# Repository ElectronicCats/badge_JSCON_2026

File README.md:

# Badge JSCONF 2026

Hardware abierto del **badge de JSCONF México 2026** (Guadalajara, 29 y 30 de octubre), diseñado por [Electronic Cats](https://electroniccats.com).

Es un nodo de radio **LoRa** con pantalla a color y cuatro botones que funciona como un nodo más de una red [Meshtastic](https://meshtastic.org): sirve de gafete con tu nombre, manda mensajes de texto a otros badges sin red celular ni Wi-Fi, y trae un juego de ajolotes que se desbloquean al encontrarte con otras personas.

Este repositorio contiene el **diseño de hardware** (esquemático, PCB y huellas). El firmware, las herramientas y la presentación del taller viven en otros repositorios (ver [Proyectos relacionados](#proyectos-relacionados)).

## Características

| Elemento | Detalle |
|-|-|
| Microcontrolador | ESP32-S3-WROOM-1-N8 (8 MB de flash, sin PSRAM), USB nativo |
| Radio | Módulo LoRa de 915 MHz (LLCC68), antena por conector SMA de borde |
| Pantalla | 428 × 142 px a color, conector FFC de 10 pines |
| Botones | 4 de usuario (arriba, abajo, select, back) y un interruptor de encendido |
| Alimentación | USB-C, con fusible de 0.75 A y regulador de 3.3 V. Sin batería ni GPS |
| Conectividad | LoRa (malla), Bluetooth LE (app de Meshtastic) y USB CDC (control desde el navegador) |
| PCB | 2 capas, 1.6 mm, diseñada en KiCad 10 |

## Estructura del repositorio

```text
.
├── hardware/                        # Proyecto de KiCad
│   ├── Badge_JSCON_2026.kicad_pro
│   ├── Badge_JSCON_2026.kicad_sch   # Esquemático
│   ├── Badge_JSCON_2026.kicad_pcb   # PCB
│   ├── Footprints/                  # Huellas, símbolos y modelos 3D propios
│   ├── fp-lib-table
│   ├── electroniccats_sch.kibot.yaml
│   └── electroniccats_pcb.kibot.yaml
├── docs/images/                     # Fotos del badge para este README
└── .github/workflows/               # Generación automática de archivos de fabricación
```

## Hardware

### KiCad

El hardware se diseña en **KiCad 10** (el proyecto fue guardado con la versión 10.0). Los archivos que genera el diseño son:

- `Badge_JSCON_2026.kicad_pro`
- `Badge_JSCON_2026.kicad_pcb`
- `Badge_JSCON_2026.kicad_sch`

Los archivos temporales de KiCad los ignora Git ([archivos ignorados](.gitignore)). Todo lo del diseño va dentro de la carpeta [hardware](hardware/).

Las huellas y símbolos que no vienen en las bibliotecas estándar (módulo LoRa, pantalla, conector USB-C, antena SMA, interruptor, ESP32-S3) están en [hardware/Footprints](hardware/Footprints/) y se cargan con `fp-lib-table`.

### Componentes principales

| Ref. | Valor | Función |
|-|-|-|
| U1 | ESP32-S3-WROOM-1-N8 | Microcontrolador, Bluetooth LE y USB |
| U5 | VGdd79S915N0S1 | Módulo LoRa 915 MHz |
| U2 | BL8072CLTR33 (SOT-223) | Regulador de 3.3 V |
| P1 | USB-C (C393939) | Alimentación y datos |
| F1 | Fusible 0.75 A | Protección de entrada |
| J2 | FFC 10 pines (Hirose FH12) | Pantalla |
| Q2 | BC846 | Control de brillo de la pantalla (`LCD_BRIGHT`) |
| SW1, SW2, SW4–SW7 | Pulsadores SMD TL3342 | Cuatro botones de usuario, BOOT y EN (reset) |
| SW3 | MSK12C02 | Interruptor de encendido |
| AE1 | Conector SMA de borde | Antena LoRa |
| R1, R2 | 5.1 kΩ | Configuración del USB-C |

La lista completa de materiales (BOM) se genera automáticamente en cada release.

### Configuración de automatización

Los workflows de GitHub Actions detectan automáticamente los archivos de KiCad en `hardware/`; no hace falta modificar ningún archivo de configuración.

Buscan:
- El primer archivo `.kicad_pcb` encontrado en `hardware/`.
- El archivo `.kicad_sch` que coincida con el nombre del PCB.
- Si no hay coincidencia exacta, el primer `.kicad_sch` disponible.

**Nota**: los archivos de KiCad deben estar en la carpeta `hardware/` con sus extensiones correctas (`.kicad_pro`, `.kicad_pcb`, `.kicad_sch`).

**Workflows disponibles:**
- **DRC y ERC**: se ejecutan en cada `push` y `pull_request` para validar el diseño.
- **Archivos de fabricación**: se generan cuando se publica un `release`.

#### Activar o desactivar DRC y ERC

Están activos por defecto. Para desactivarlos, cambia estas líneas en [electroniccats_sch.kibot.yaml](hardware/electroniccats_sch.kibot.yaml):

```yaml
run_erc: false  # Cambiar a false para desactivar ERC
run_drc: false  # Cambiar a false para desactivar DRC
```

### Creación de un release

Al terminar el proyecto y su revisión se publica el release:

1. Presiona **Create a new release**.
2. Revisa la sección de **Actions**: ahí se generan los archivos.
3. Al terminar, los archivos de fabricación (Gerbers, taladros, BOM y BOM interactivo, posición de componentes, modelo STEP y PDF del esquemático y del PCB) quedan adjuntos al mismo release.

## Cómo funciona el badge

Con el firmware del taller, el badge:

- Se anuncia en las apps de Meshtastic como un nodo normal (por Bluetooth LE, con PIN de 6 dígitos que muestra la pantalla).
- Usa el preset `SHORT_FAST` en la región US, fijos. Por eso **no interopera con la malla pública** de Meshtastic, solo con otros badges del evento.
- Se puede controlar desde el navegador por USB con Web Serial (mostrar textos, pulsar botones, cambiar el nombre, subir una imagen de 428 × 142).

Los detalles del firmware, el juego de ajolotes, las páginas de la pantalla y cómo flashear un badge están en el repositorio del firmware.

## Proyectos relacionados

| Proyecto | Qué contiene |
|-|-|
| [jscon-2026-firmware](https://github.com/ElectronicCats/jscon-2026-firmware) | Firmware (fork de Meshtastic con el target `badge_jscon2026`) |
| [presentacion-jscon-2026](https://github.com/ElectronicCats/presentacion-jscon-2026) | Presentación del taller |
| [Tienda de Electronic Cats](https://electroniccats.com/store/badgejsconf-taller/) | Badge y taller de JSCONF |
| [JSCONF México](https://www.jsconf.mx/) | Evento |

## Licencia y créditos

- **Diseño de hardware:** Lizeth Gallegos Martínez, Electronic Cats (rev. v1.0).
- **Presentadores del taller:** Andrés Sabas y Heikki Isa Perea Esparza.
- **Evento:** JSCONF México 2026.

## Maintainer

Electronic Cats invests time and resources providing this open source design, please support Electronic Cats and open-source hardware by purchasing products from Electronic Cats!

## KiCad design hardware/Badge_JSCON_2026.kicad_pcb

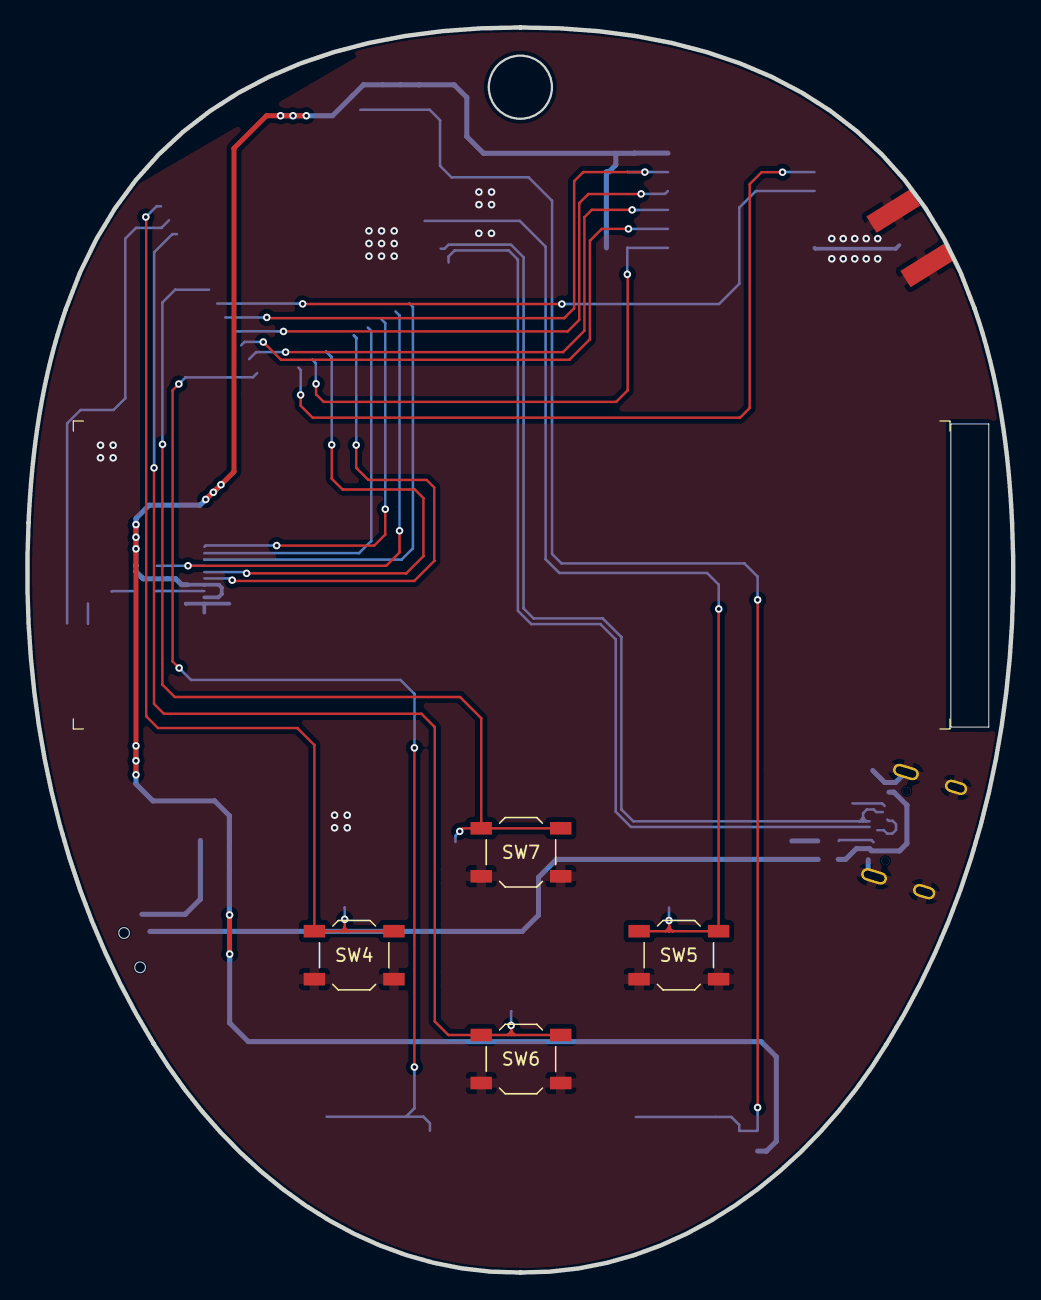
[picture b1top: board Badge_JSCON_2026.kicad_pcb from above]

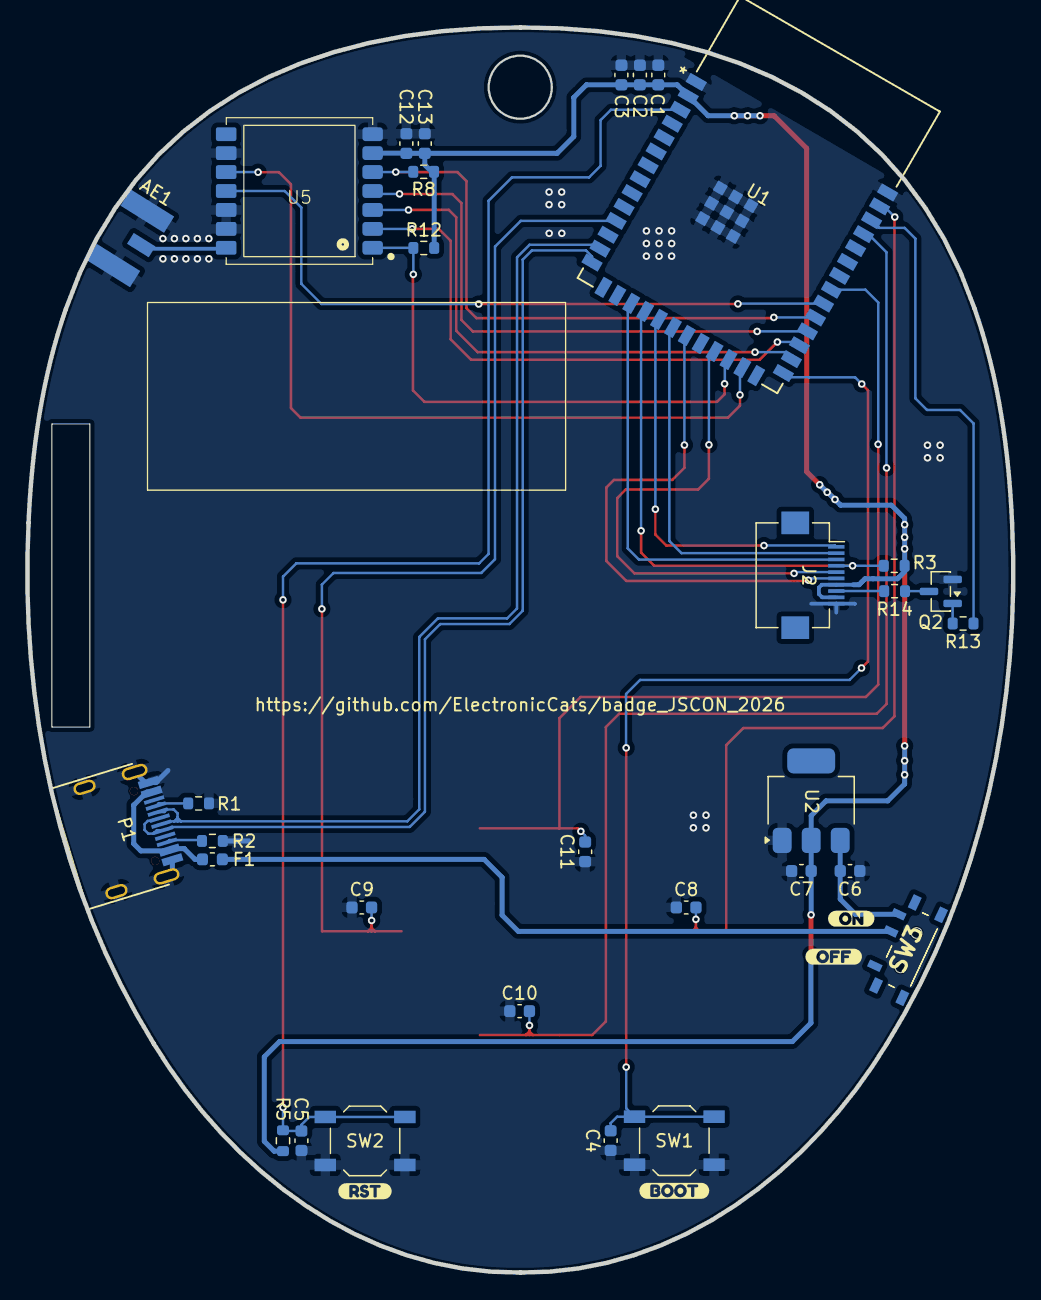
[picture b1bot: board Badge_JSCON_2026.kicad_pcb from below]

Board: 2 copper layers, 78.1 x 98.6 mm, 40 parts (36 on the bottom side), 33 nets.

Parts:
AE1: Antenna_Shield; SMA_EDGE
C1: 1uF; C_0603_1608Metric
C2, C3, C6, C7, C13: 10uF; C_0603_1608Metric
C4, C5, C8, C9, C10, C11: 0.1uF; C_0603_1608Metric
C12: 100nF; C_0603_1608Metric
F1: 0.75A; Fuse_0603_1608Metric
J2: LCD; Hirose_FH12-10S-0.5SH_1x10-1MP_P0.50mm_Horizontal
P1: USB_C_Plug_USB2.0; C393939
Q2: BC846; SOT-23
R1, R2: 5k1; R_0603_1608Metric
R3, R5, R8, R12: 10K; R_0603_1608Metric
R13: 1K; R_0603_1608Metric
R14: 3.9r; R_0603_1608Metric
SW1, SW2, SW4, SW5, SW6, SW7: SW_SPST_TL3342
SW3: ON; MSK12C02
U1: ESP32-S3-WROOM-1-N8; ESP32-S3-WROOM-1_EXP
U2: BL8072CLTR33; SOT-223
U5: VGdd79S915N0S1
kibuzzard-6A3B026D: G***; kibuzzard-6A3B026D
kibuzzard-6A3B0259: G***; kibuzzard-6A3B0259
kibuzzard-6A3B0260: G***; kibuzzard-6A3B0260
kibuzzard-6A3B0265: G***; kibuzzard-6A3B0265

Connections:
+3.3V: C1.1, C2.1, C3.1, C7.1, C12.1, C13.1, J2.7, J2.9, R3.2, R5.2, R8.2, R12.2, U1.2 (3V3), U2.2 (VO), U5.6 (VCC)
/BOOT: C4.2, SW1.2, U1.27 (IO0)
/BUSY: U1.32 (IO39), U5.11 (BUSY)
/CS0: R8.1, U1.31 (IO38), U5.5 (NSS)
/CS1: J2.4, R3.1, U1.18 (IO10)
/D+: P1.A6 (D+), U1.14 (IO20)
/D-: P1.A7 (D-), U1.13 (IO19)
/DIO: U1.25 (IO48), U5.10 (DIO1)
/DOWN: C10.2, SW6.2, U1.37 (TXD0)
/EN: C5.2, R5.1, SW2.2, U1.3 (EN)
/LCD_BRIGHT: R13.1, U1.38 (IO2)
/LEDK: J2.8, R14.2
/LEFT: C8.2, SW4.2, U1.39 (IO1)
/MISO: U1.29 (IO36), U5.2 (MISO)
/MOSI: U1.28 (IO35), U5.3 (MOSI)
/RIGHT: C9.2, SW5.2, U1.11 (IO18)
/RS: J2.3, U1.17 (IO9)
/RST: R12.1, U1.24 (IO47), U5.1 (RST)
/RSTB: J2.5, U1.23 (IO21)
/SCK: U1.30 (IO37), U5.4 (SCK)
/SPI_MOSI: J2.1, U1.19 (IO11)
/SPI_SCLK: J2.2, U1.20 (IO12)
/TE: J2.6, U1.21 (IO13)
/UP: C11.2, SW7.2, U1.33 (IO40)
GND: AE1.2 (Shield), C1.2, C2.2, C3.2, C4.1, C5.1, C6.2, C7.2, C8.1, C9.1, C10.1, C11.1, C12.2, C13.2, J2.10, P1.A1 (GND), P1.S1 (SHIELD), Q2.2 (E), R1.1, R2.1, SW1.1, SW2.1, SW4.1, SW5.1, SW6.1, SW7.1, U1.1 (GND), U1.40 (GND), U1.41 (GND), U1.42 (GND), U1.43 (GND), U1.44 (GND), U1.45 (GND), U1.46 (GND), U1.47 (GND), U1.48 (GND), U1.49 (GND), U2.1 (GND), U5.7 (GND), U5.9 (GND), U5.12 (GND), U5.13 (GND)
unnamed: AE1.1 (A), U5.14 (ANT)
unnamed: F1.1, P1.A4 (VBUS)
unnamed: P1.A5 (CC), R1.2
unnamed: P1.B5 (VCONN), R2.2
unnamed: Q2.1 (B), R13.2
unnamed: Q2.3 (C), R14.1
unnamed: C6.1, SW3.3 (A), U2.3 (VI)
VBUS: F1.2, SW3.2 (B)

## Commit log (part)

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2026-05-29 feat(Hw):Init_schematic
2026-06-18 feat(Hw):Update_Files
2026-06-18 feat(Hw):Init_Floorplan
2026-06-19 feat(Hw):Init_Route
2026-06-22 feat(Hw):Update_Route
2026-06-23 feat(Hw):Update_Labels
2026-06-30 fix: resistor 10k price
2026-06-30 fix: file pro
